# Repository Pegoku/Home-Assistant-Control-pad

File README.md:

# Home-Assistant-Control-pad

This is a programmable Home Assistant Control Pad. It can control 4 Home assistant devices at a time, and has 4 togglable screens/zones (in total 16 devices). It uses buttons and rotary encoders to enable and control other HASS devices. It also has an OLED Display (1.33") to display the status of the devices. It is battery powered, it contains a 1800mAh Li-Po. The device uses an ESP32-S2 and ESPHome.

## Why I made it?

I made this project as I wanted an easy and fast way to control the "smart" devices I have made. I'm making quite a few ESPHome devices and wanted something to control most of them easily.

## Features

- Controls Home Assistant entities (lights, switches, etc.)
- Over-the-air (OTA) updates

## Images

Final Build: 

<details>
  <summary>Case</summary>

</details>
<details>
  <summary>Schematic</summary>

</details>
<details>
  <summary>PCB</summary>

</details>

## BOM

| Index | Part Number                               | What the item is for in your project             | Description                          | Pack Quantity | ID                                                                                      | Unit Price | Total Price | Total   |
| ----- | ----------------------------------------- | ------------------------------------------------ | ------------------------------------ | ------------- | --------------------------------------------------------------------------------------- | ---------- | ----------- | ------- |
| 1     | PMEG10010ELRX                             | Reverse polarity protection                      | DIODE SCHOTTKY 100V 1A SOD123W       | 2             | 1727+AC0-2394+AC0-1+AC0-ND                                                              | $0.27      | $0.54       | $133.08 |
| 2     | DFE252012P+AC0-1R0M+AD0-P2                | Inductor for buck+AC0-boost                      | FIXED IND 1UH 3.2A 0.042OHM SMD      | 3             | 490+AC0-10647+AC0-1+AC0-ND                                                              | $0.22      | $0.66       |
| 3     | LS R976+AC0-NR+AC0-1+AC0-0+AC0-20+AC0-R18 | Led indication                                   | LED RED DIFFUSED 0805 SMD            | 3             | 475+AC0-LSR976+AC0-NR+AC0-1CT+AC0-ND                                                    | $0.15      | $0.45       |
| 4     | LG R971+AC0-KN+AC0-1+AC0-0+AC0-20+AC0-R18 | Led indication                                   | LED GREEN DIFFUSED 0805 SMD          | 3             | 475+AC0-LGR971+AC0-KN+AC0-1CT+AC0-ND                                                    | $0.15      | $0.45       |
| 5     | LTST+AC0-C170KSKT                         | Led indication                                   | LED YELLOW CLEAR SMD                 | 3             | 160+AC0-1416+AC0-1+AC0-ND                                                               | $0.17      | $0.51       |
| 6     | RMCF0603JT10K0                            | Passive                                          | RES 10K OHM 5% 1/10W 0603            | 22            | RMCF0603JT10K0CT+AC0-ND                                                                 | $0.02      | $0.42       |
| 7     | CRCW06035K11FKEAC                         | Passive                                          | RES 5.11K OHM 1% 1/10W 0603          | 3             | 541+AC0-5491+AC0-1+AC0-ND                                                               | $0.10      | $0.30       |
| 8     | RC0402FR+AC0-071KL                        | Passive                                          | RES 1K OHM 1% 1/16W 0402             | 2             | 311+AC0-1.00KLRCT+AC0-ND                                                                | $0.10      | $0.20       |
| 9     | RC0402FR+AC0-07470RL                      | Passive                                          | RES 470 OHM 1% 1/16W 0402            | 4             | 311+AC0-470LRCT+AC0-ND                                                                  | $0.10      | $0.40       |
| 10    | RC0603FR+AC0-07511KL                      | Passive                                          | RES 511K OHM 1% 1/10W 0603           | 2             | 311+AC0-511KHRCT+AC0-ND                                                                 | $0.10      | $0.20       |
| 11    | RC0603FR+AC0-0791KL                       | Passive                                          | RES 91K OHM 1% 1/10W 0603            | 3             | 311+AC0-91.0KHRCT+AC0-ND                                                                | $0.10      | $0.30       |
| 12    | RC0603FR+AC0-07806KL                      | Passive                                          | RES 806K OHM 1% 1/10W 0603           | 2             | 311+AC0-806KHRCT+AC0-ND                                                                 | $0.10      | $0.20       |
| 13    | RC0603FR+AC0-071KL                        | Passive                                          | RES 1K OHM 1% 1/10W 0603             | 13            | 311+AC0-1.00KHRCT+AC0-ND                                                                | $0.01      | $0.12       |
| 14    | RC0603FR+AC0-073K9L                       | Passive                                          | RES 3.9K OHM 1% 1/10W 0603           | 2             | 311+AC0-3.90KHRCT+AC0-ND                                                                | $0.10      | $0.20       |
| 15    | RC0402FR+AC0-071K54L                      | Passive                                          | RES 1.54K OHM 1% 1/16W 0402          | 2             | YAG3040CT+AC0-ND                                                                        | $0.10      | $0.20       |
| 16    | RC0402FR+AC0-0769K8L                      | Passive                                          | RES 69.8K OHM 1% 1/16W 0402          | 2             | YAG3216CT+AC0-ND                                                                        | $0.10      | $0.20       |
| 17    | PEC11R+AC0-4220F+AC0-S0024                | Rotate action                                    | ROTARY ENCODER MECHANICAL 24PPR      | 7             | PEC11R+AC0-4220F+AC0-S0024+AC0-ND                                                       | $1.89      | $13.23      |
| 18    | PTS815SJG250SMTR LFS                      | Esp32 buttons                                    | SWITCH TACTILE SPST+AC0-NO 0.05A 12V | 3             | CKN12217+AC0-1+AC0-ND                                                                   | $0.28      | $0.84       |
| 19    | TX08F103F3435ER                           | NTC Thermistor                                   | THERMISTOR 0805 10K/3435             | 2             | 273+AC0-TX08F103F3435ERCT+AC0-ND                                                        | $0.12      | $0.24       |
| 20    | ESP32+AC0-S2+AC0-MINI+AC0-2+AC0-N4R2      | MCU                                              | RF TXRX MOD WIFI PCB TRACE SMD       | 2             | 1965+AC0-ESP32+AC0-S2+AC0-MINI+AC0-2+AC0-N4R2CT+AC0-ND                                  | $4.31      | $8.62       |
| 21    | MCP73833T+AC0-FCI/MF                      | Battery charger                                  | IC BATT CONTRL LI+AC0-ION 1CEL 10DFN | 2             | MCP73833T+AC0-FCI/MFCT+AC0-ND                                                           | $1.14      | $2.28       |
| 22    | TPS631010YBGR                             | Buck+AC0-Boost                                   | IC REG BUCK BST ADJ 1.5A 8DSBGA      | 3             | 296+AC0-TPS631010YBGRCT+AC0-ND                                                          | $1.29      | $3.87       |
| 23    | C0603C103J5REC7411                        | Passive                                          | CAP CER SMD 0603 .01UF 5% X7R 50     | 13            | 399+AC0-17568+AC0-1+AC0-ND                                                              | $0.10      | $1.33       |
| 24    | C0603C104J5REC7411                        | Passive                                          | CAP CER 0603                         | 20            | 399+AC0-C0603C104J5REC7411CT+AC0-ND                                                     | $0.11      | $2.24       |
| 25    | CL10A105KQ8NNNC                           | Passive                                          | CAP CER 1UF 6.3V X5R 0603            | 2             | 1276+AC0-1036+AC0-1+AC0-ND                                                              | $0.10      | $0.20       |
| 26    | CL10A106KQ8NNNC                           | Passive                                          | CAP CER 10UF 6.3V X5R 0603           | 13            | 1276+AC0-1038+AC0-1+AC0-ND                                                              | $0.03      | $0.39       |
| 27    | CL21A476MQYNNNG                           | Passive                                          | CAP CER 47UF 6.3V X5R 0805           | 15            | 1276+AC0-6467+AC0-1+AC0-ND                                                              | $0.16      | $2.37       |
| 28    | 16347                                     | Led indication                                   | ADDRESS LED RED/GRN/BLUE             | 5             | 1568+AC0-16347CT+AC0-ND                                                                 | $0.68      | $3.40       |
| 29    | B3F+AC0-4055                              | Push Action                                      | SWITCH TACTILE SPST+AC0-NO 0.05A 24V | 10            | SW414+AC0-ND                                                                            | $0.42      | $4.23       |
| 30    | S2B+AC0-PH+AC0-K+AC0-S                    | Battery connector                                | CONN HEADER R/A 2POS 2MM             | 2             | 455+AC0-1719+AC0-ND                                                                     | $0.11      | $0.22       |
| 31    | PCB                                       | PCB                                              |                                      | 1             | https://aisler.net                                                                      | $42.57     | $42.57      |
| 32    | Battery                                   | Power Source                                     | 103450 1800mAh                       | 1             | https://www.ebay.es/itm/255510046348                                                    | $15.44     | $15.44      |
| 33    | Display                                   | Displays The UI                                  | I2C display                          | 1             | https://es.aliexpress.com/item/1005006862867338.html                                    | $2.62      | $2.62       |
| 34    | Rubber Feet                               | Adds friction to the base so it doesn+IBk-t slip |                                      | 1             | https://es.aliexpress.com/item/1005005275590870.html                                    | $3.11      | $3.11       |
| 35    | ELEGOO PLA filament                       | Printing case                                    |                                      | 1             | https://www.amazon.es/-/en/Filament-Printer-Dimensional-Accuracy-Printers/dp/B0CD77VHBZ | $20.53     | $20.53      |

## Configuration

Remember to set your secrets in [secrets.yaml](Code/secrets.example.yaml).

All firmware configuration lives in [code.yaml](Code/code.yaml):
PS: This configuration is for reference only, The final configuration will be for the ESP32-S2. You'll also have to configure the devices you want to control in Home Assistant.
```yaml
esphome:
  name: controlpad
  friendly_name: ControlPad

esp32:
  board: esp32-c3-devkitm-1
  framework:
    type: arduino

# Enable logging
logger:

# Enable Home Assistant API
api:
  encryption:
    key: !secret api_key

ota:
  - platform: esphome
    password: !secret ota_password

wifi:
  ssid: !secret wifi_ssid
  password: !secret wifi_password

  # Enable fallback hotspot (captive portal) in case wifi connection fails
  ap:
    ssid: "Controlpad Fallback Hotspot"
    password: "wHjqyQOLnaPa"

globals:
  - id: page_active
    type: int
    initial_value: "0"

i2c:
  sda: GPIO6
  scl: GPIO7
  frequency: 800kHz
  scan: true

binary_sensor:
  - platform: gpio
    pin:
      number: GPIO2
      mode: INPUT_PULLUP
      inverted: true
    name: "Button1"
    on_press:
      - display.page.show: page1
      - lambda: |-
          id(page_active) = 1;

  - platform: gpio
    pin:
      number: GPIO4
      mode: INPUT_PULLUP
      inverted: true
    name: "Button2"
    on_press:
      - display.page.show: page2
      - lambda: |-
          id(page_active) = 2;

  - platform: gpio
    pin:
      number: GPIO21
      mode: INPUT_PULLUP
      inverted: true
    name: "toggle1"
    on_press:
      then:
        - if:
            condition:
              lambda: |-
                return id(page_active) == 1;
            then:
              - homeassistant.service:
                  service: light.toggle
                  data:
                    entity_id: light.led_controller_1_light_bar

sensor:
  - platform: homeassistant
    name: "Bar Light Brightness"
    id: led_controller_1_light_bar_brightness
    entity_id: light.led_controller_1_light_bar
    attribute: brightness
    unit_of_measurement: "%"
    filters:
      - lambda: |-
          if (isnan(x)) return 0.0f;
          return int(x * 100.0f / 255.0f);

  - platform: adc
    pin: GPIO3
    name: "potentiometer1"
    id: potentiometer1
    attenuation: 12db # allow 0–3.3 V range
    update_interval: 20ms
    unit_of_measurement: "%"
    filters:
      - sliding_window_moving_average:
          window_size: 10
          send_every: 5
      - lambda: |-
          if (isnan(x)) return 0.0f;
          int pot_val = int(x * 100.0f / 2.9f);
          if (pot_val > 100) pot_val = 100;
          return pot_val;
      - delta: 1.0

    on_value:
      then:
        - if:
            condition:
              lambda: |-
                return id(page_active) == 1;
            then:
              - homeassistant.service:
                  service: light.turn_on
                  data:
                    entity_id: light.led_controller_1_light_bar
                    brightness_pct: !lambda "return (int)x;"

# SH1106 128×64 over I2C
display:
  - platform: ssd1306_i2c
    model: SH1106 128x64
    id: display1
    address: 0x3C
    rotation: 0
    update_interval: 100ms
    pages:
      - id: page1
        lambda: |-
          int val1 = int((id(led_controller_1_light_bar_brightness).state / 100.0f) * 31);
          if (val1 != 0) {
            val1 += 1;
          }
          it.filled_rectangle(10, 64-val1, 5, 33);

          // it.printf(0, 0, id(font1), "%.0f%%", id(led_controller_1_light_bar_brightness).state);
      - id: page2
        lambda: |-
          it.print(0, 10, id(font1), "This is page 2!");
          it.filled_rectangle(10, 20, 80, 5);

font:
  - file: "gfonts://Ubuntu"
    id: font1
    size: 20

captive_portal:
```

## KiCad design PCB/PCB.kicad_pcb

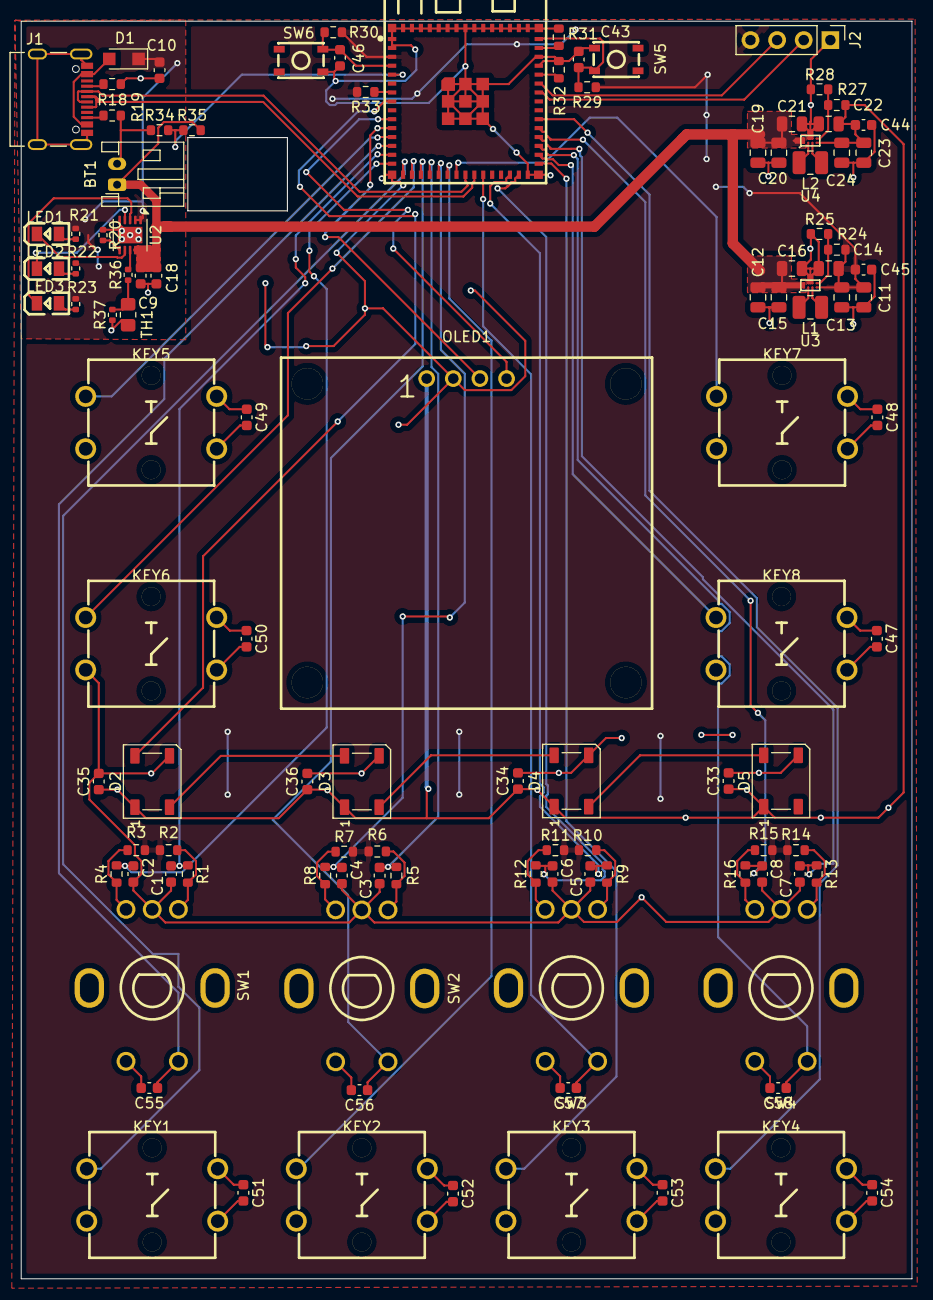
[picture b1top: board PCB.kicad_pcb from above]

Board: 2 copper layers, 85.0 x 120.0 mm, 111 parts (0 on the bottom side), 83 nets.

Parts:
BT1: 2Ah; JST_PH_S2B-PH-K_1x02_P2.00mm_Horizontal
C1, C2, C3, C4, C5, C6, C7, C8: 0.01uF; C_0603_1608Metric
C9: 1uF; C_0603_1608Metric
C10, C18, C33, C34, C35, C36: 10uF; C_0603_1608Metric
C11, C12, C13, C14, C15, C16, C19, C20, C21, C22, C23, C24: 47uF; C_0805_2012Metric
C43, C44, C45, C46, C47, C48, C49, C50, C51, C52, C53, C54, C55, C56, C57, C58: 0.1uF; C_0603_1608Metric
D1: D; Nexperia_CFP3_SOD-123W
D2, D3, D4, D5: WS2812B; LED_WS2812B_PLCC4_5.0x5.0mm_P3.2mm
J1: 10155435-00011LF; AMPHENOL_10155435-00011LF
J2: Conn_01x04_Pin; PinHeader_1x04_P2.54mm_Vertical
KEY1, KEY2, KEY3, KEY4, KEY5, KEY6, KEY7, KEY8: B3F-4055; KEY-TH_4P-L12.0-W12.0-P5.00-LS13.4-EH
L1, L2: 1uH; L_1008_2520Metric
LED1, LED2, LED3: FC-2012HRK-620D; LED0805-R-RD
OLED1: HS13L03W2C01; OLED-TH_L35.4-W33.5_HS13L03W2C01
R1, R2, R3, R4, R5, R6, R7, R8, R9, R10, R11, R12, R13, R14, R15, R16, R34: 10k; R_0603_1608Metric
R18, R19: 5.11k; R_0603_1608Metric
R20: 1k; R_0402_1005Metric
R21, R22, R23: 470; R_0402_1005Metric
R24: 511k; R_0603_1608Metric
R25, R28: 91k; R_0603_1608Metric
R27: 806k; R_0603_1608Metric
R29, R30, R31, R32, R33: 1k; R_0603_1608Metric
R35: 3.9K; R_0603_1608Metric
R36: 1.54k; R_0402_1005Metric
R37: 69.8k; R_0402_1005Metric
SW1, SW2, SW3, SW4: PEC11R-4220F-S0024; SW-TH_5P-L12.5-W13.4-P2.50-LS14.5-EH13.2
SW5, SW6: PTS815SJM250SMTRLFS; KEY-SMD_4P-L4.2-W3.25-P2.15-TL
TH1: 10k; R_0805_2012Metric_Pad1.20x1.40mm_HandSolder
U1: ESP32-S2-MINI-2-N4R2; WIFI-SMD_ESP32-MINI-1-N4
U2: MCP73833-xxx-MF; DFN-10-1EP_3x3mm_P0.5mm_EP1.58x2.35mm
U3, U4: TPS631010YBGR; WLCSP-8_L1.8-W1.0-R4-C2-P0.40-BR

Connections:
+3.3V: C11.1, C13.1, C14.1, C45.1, J2.4, R2.2, R3.2, R6.2, R7.2, R10.2, R11.2, R14.2, R15.2, R24.1, R29.1, R30.1, R33.2, U1.3 (3V3), U3.D1 (VOUT)
+5V: C22.1, C23.1, C24.1, C33.1, C34.1, C35.1, C36.1, C44.1, D2.1 (VDD), D3.1 (VDD), D4.1 (VDD), D5.1 (VDD), OLED1.1 (VDD), R27.1, U4.D1 (VOUT)
+BATT: BT1.1 (+), C9.1, C12.1, C15.1, C16.1, C18.1, C19.1, C20.1, C21.1, R35.2, U2.9 (V_{BAT}), U2.10 (V_{BAT}), U3.A1 (VIN), U3.A2 (EN), U4.A1 (VIN), U4.A2 (EN)
Action_1_SW: KEY1.4, U1.16 (IO12)
Action_2_SW: KEY2.4, U1.21 (IO17)
Action_3_SW: KEY3.4, U1.31 (IO35)
Action_4_SW: KEY4.4, U1.36 (IO40)
BOOT: C46.1, R30.2, SW6.2, U1.4 (IO0)
DN: J1.A7 (DN1), J1.B7 (DN2), U1.23 (IO19)
DP: J1.A6 (DP1), J1.B6 (DP2), U1.24 (IO20)
EN: C43.1, R29.2, SW5.2, U1.45 (EN)
Enc_1_A: C1.1, R1.1, U1.14 (IO10)
Enc_1_B: C2.1, R4.2, U1.15 (IO11)
Enc_1_SW: C55.1, SW1.4 (1), U1.13 (IO9)
Enc_2_A: C3.1, R5.1, U1.19 (IO15)
Enc_2_B: C4.1, R8.2, U1.20 (IO16)
Enc_2_SW: C56.1, SW2.4 (1), U1.18 (IO14)
Enc_3_A: C5.1, R9.1, U1.28 (IO33)
Enc_3_B: C6.1, R12.2, U1.29 (IO34)
Enc_3_SW: C57.1, SW3.4 (1), U1.25 (IO21)
Enc_4_A: C7.1, R13.1, U1.34 (IO38)
Enc_4_B: C8.1, R16.2, U1.35 (IO39)
Enc_4_SW: C58.1, SW4.4 (1), U1.33 (IO37)
GND: BT1.2 (-), C1.2, C2.2, C3.2, C4.2, C5.2, C6.2, C7.2, C8.2, C9.2, C10.2, C11.2, C12.2, C13.2, C14.2, C15.2, C16.2, C18.2, C19.2, C20.2, C21.2, C22.2, C23.2, C24.2, C33.2, C34.2, C35.2, C36.2, C43.2, C44.2, C45.2, C46.2, C55.2, C56.2, C57.2, C58.2, D2.3 (VSS), D3.3 (VSS), D4.3 (VSS), D5.3 (VSS), J1.A1_B12 (GND), J1.B1_A12 (GND__1), J1.SH1 (SHIELD), J1.SH2 (SHIELD__1), J1.SH3 (SHIELD__2), J1.SH4 (SHIELD__3), J2.1, KEY1.2, KEY2.2, KEY3.2, KEY4.2, KEY5.2, KEY6.2, KEY7.2, KEY8.2, OLED1.2 (GND), R18.1, R19.2, R20.1, R25.2, R28.2, R31.2, R32.2, R34.1, R37.1, SW1.2 (C), SW1.5 (2), SW2.2 (C), SW2.5 (2), SW3.2 (C), SW3.5 (2), SW4.2 (C), SW4.5 (2), SW5.4, SW6.4, TH1.2, U1.1 (GND), U1.2 (GND), U1.30 (GND), U1.42 (GND), U1.43 (GND), U1.46 (GND), U1.47 (GND), U1.48 (GND), U1.49 (GND), U1.50 (GND), U1.51 (GND), U1.52 (GND), U1.53 (GND), U1.54 (GND), U1.55 (GND), U1.56 (GND), U1.57 (GND), U1.58 (GND), U1.59 (GND), U1.60 (GND), U1.61 (GND), U1.62 (GND), U1.63 (GND), U1.64 (GND), U1.65 (GND), U2.5 (V_{SS}), U2.11 (EP), U3.B2 (MODE), U3.C2 (GND), U4.B2 (MODE), U4.C2 (GND)
LED_Pin: D2.4 (DIN), U1.8 (IO4)
unnamed: C47.1, KEY8.3
unnamed: C47.2, KEY8.1
unnamed: C48.1, KEY7.3
unnamed: C48.2, KEY7.1
unnamed: C49.1, KEY5.3
unnamed: C49.2, KEY5.1
unnamed: C50.1, KEY6.3
unnamed: C50.2, KEY6.1
unnamed: C51.1, KEY1.3
unnamed: C51.2, KEY1.1
unnamed: C52.1, KEY2.3
unnamed: C52.2, KEY2.1
unnamed: C53.1, KEY3.3
unnamed: C53.2, KEY3.1
unnamed: C54.1, KEY4.3
unnamed: C54.2, KEY4.1
unnamed: D1.2 (A), J1.A4_B9 (VBUS), J1.B4_A9 (VBUS__1)
unnamed: D2.2 (DOUT), D3.4 (DIN)
unnamed: D3.2 (DOUT), D4.4 (DIN)
unnamed: D4.2 (DOUT), D5.4 (DIN)
unnamed: J1.A5 (CC1), R18.2
unnamed: J1.B5 (CC2), R19.1
unnamed: LED1.1 (+), R21.1
unnamed: LED1.2 (-), U2.7 (~PG)
unnamed: LED2.1 (+), R22.1
unnamed: LED2.2 (-), U2.4 (STAT2)
unnamed: LED3.1 (+), R23.1
unnamed: LED3.2 (-), U2.3 (STAT1)
unnamed: R36.1, R37.2, TH1.1
unnamed: R1.2, R2.1, SW1.1 (A)
unnamed: R3.1, R4.1, SW1.3 (B)
unnamed: R5.2, R6.1, SW2.1 (A)
unnamed: R7.1, R8.1, SW2.3 (B)
unnamed: R9.2, R10.1, SW3.1 (A)
unnamed: R11.1, R12.1, SW3.3 (B)
unnamed: R13.2, R14.1, SW4.1 (A)
unnamed: R15.1, R16.1, SW4.3 (B)
unnamed: R33.1, U1.7 (IO3)
unnamed: R32.1, U1.41 (IO45)
unnamed: R31.1, U1.44 (IO46)
unnamed: R20.2, U2.6 (PROG)
unnamed: R36.2, U2.8 (THERM)
unnamed: R24.2, R25.1, U3.D2 (FB)
unnamed: L1.1, U3.B1 (LX1)
unnamed: L1.2, U3.C1 (LX2)
unnamed: R27.2, R28.1, U4.D2 (FB)
unnamed: L2.1, U4.B1 (LX1)
unnamed: L2.2, U4.C1 (LX2)
RX: J2.3, U1.40 (RXD0)
SCL: OLED1.3 (SCL), U1.11 (IO7)
SDA: OLED1.4 (SDA), U1.10 (IO6)
TX: J2.2, U1.39 (TXD0)
VBATT_sense: R34.2, R35.1, U1.5 (IO1)
VCC: C10.1, D1.1 (K), R21.2, R22.2, R23.2, U2.1 (V_{DD}), U2.2 (V_{DD})
View_1_SW: KEY5.4, U1.12 (IO8)
View_2_SW: KEY6.4, U1.17 (IO13)
View_3_SW: KEY7.4, U1.22 (IO18)
View_4_SW: KEY8.4, U1.32 (IO36)

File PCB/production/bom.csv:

,Footprint,Quantity,Value,LCSC Part #
BT1,JST_PH_S2B-PH-K_1x02_P2.00mm_Horizontal,1,2Ah,
"C1, C2, C3, C4, C5, C6, C7, C8",0603,8,0.01uF,
"C10, C18, C33, C34, C35, C36",0603,6,10uF,
"C11, C12, C13, C14, C15, C16, C19, C20, C21, C22, C23, C24",0805,12,47uF,
"C43, C44, C45, C46, C47, C48, C49, C50, C51, C52, C53, C54, C55, C56, C57, C58",0603,16,0.1uF,
C9,0603,1,1uF,
D1,Nexperia_CFP3_SOD-123W,1,D,
"D2, D3, D4, D5",LED_WS2812B_PLCC4_5.0x5.0mm_P3.2mm,4,WS2812B,
J1,AMPHENOL_10155435-00011LF,1,10155435-00011LF,
J2,PinHeader_1x04_P2.54mm_Vertical,1,Conn_01x04_Pin,
"KEY1, KEY2, KEY3, KEY4, KEY5, KEY6, KEY7, KEY8",KEY-TH_4P-L12.0-W12.0-P5.00-LS13.4-EH,8,B3F-4055,C84931
"L1, L2",1008,2,1uH,
"LED1, LED2, LED3",LED0805-R-RD,3,FC-2012HRK-620D,C84256
OLED1,OLED-TH_L35.4-W33.5_HS13L03W2C01,1,HS13L03W2C01,C7465997
"R1, R10, R11, R12, R13, R14, R15, R16, R2, R3, R34, R4, R5, R6, R7, R8, R9",0603,17,10k,
"R18, R19",0603,2,5.11k,
R20,0402,1,1k,
"R21, R22, R23",0402,3,470,
R24,0603,1,511k,
"R25, R28",0603,2,91k,
R27,0603,1,806k,
"R29, R30, R31, R32, R33",0603,5,1k,
R35,0603,1,3.9K,
R36,0402,1,1.54k,
R37,0402,1,69.8k,
"SW1, SW2, SW3, SW4",SW-TH_5P-L12.5-W13.4-P2.50-LS14.5-EH13.2,4,PEC11R-4220F-S0024,C143797
"SW5, SW6",KEY-SMD_4P-L4.2-W3.25-P2.15-TL,2,PTS815SJM250SMTRLFS,C2689510
TH1,0805,1,10k,
U1,WIFI-SMD_ESP32-MINI-1-N4,1,ESP32-S2-MINI-2-N4R2,C3013908
U2,DFN-10-1EP_3x3mm_P0.5mm_EP1.58x2.35mm,1,MCP73833-xxx-MF,
"U3, U4",WLCSP-8_L1.8-W1.0-R4-C2-P0.40-BR,2,TPS631010YBGR,C6719123

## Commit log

2025-05-18 JOURNAL
2025-05-19 working 1 potentiometer and only when screen 1
2025-05-20 add button for D1
2025-05-20 remove text, use a bar to indicate status
2025-06-06 README
2025-06-06 fix readme
2025-08-04 working code (except display)
2025-08-06 Finish project
2025-08-06 Add image to readme
2025-08-06 Create LICENSE
